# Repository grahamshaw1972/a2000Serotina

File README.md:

# A2000 Serotina Mechanical Keyboard

The A2000 Serotina Keyboard is a build it yourself Open Source Hardware Mechanical Keyboard for the Amiga A2000 and A3000 computers. Features are:

- Uses standard PC keyboard parts, case + keycaps

- Allows the use of the WASD keycap printing service for Amiga specific keycaps

- All soldering is Through Hole - no SMD soldering required

- No original A2000 keyboard parts required

- All electronic components are still available to buy

- Uses an Arduino micro-controller

- Uses Cherry MX type switches

- Uses QMK firmware ( with Amiga specific code added )

- Multiple QMK keymaps supported for regional key variations

- Plugs directly in to an A2000 or A3000 using the 5 pin Din connector - no USB required

Jan Beta has done an excellent build video for this keyboard. Please take a look:
https://youtu.be/dw3RDYq1Pn0?si=XJSP298tZxawzPFw

The keyboard layout for the UK keymap looks like this: 

The PCB for V1.5 looks like this: 

When the build is completed, V1.4 looks like this: 

A family portrait. The V1.4 Serotina keyboard with it's bigger brother and the inspiration for the project.

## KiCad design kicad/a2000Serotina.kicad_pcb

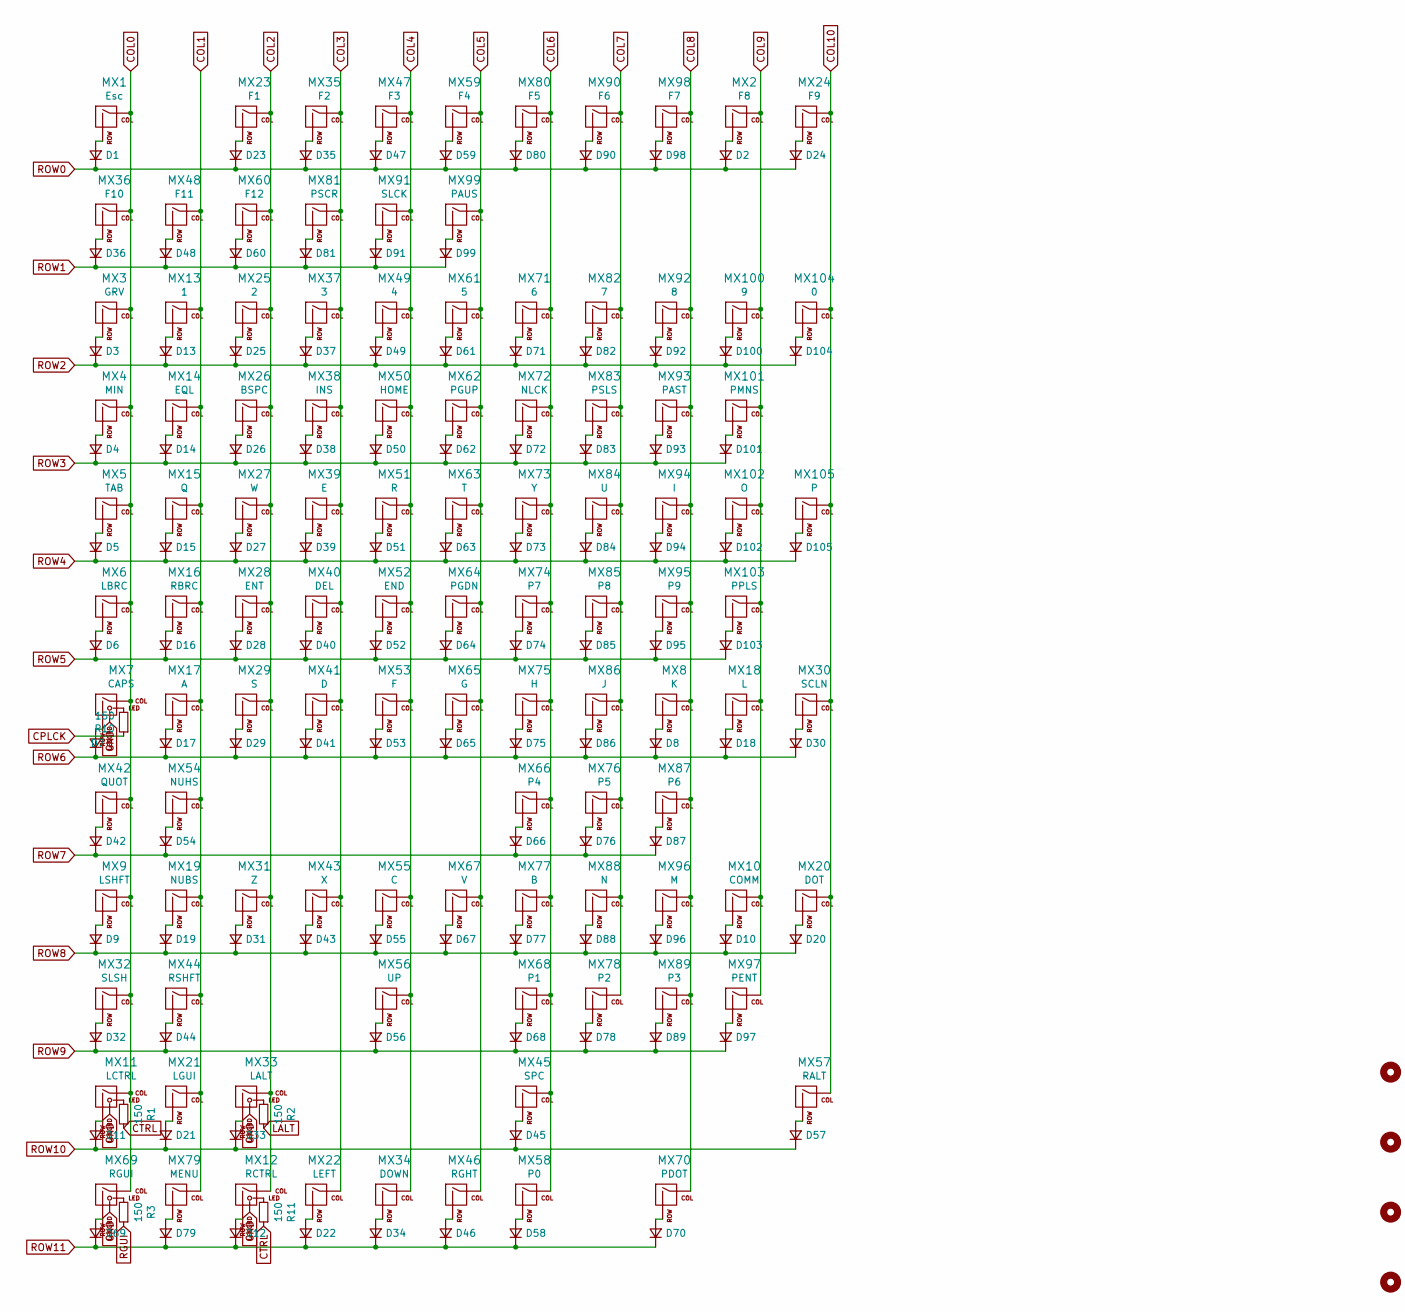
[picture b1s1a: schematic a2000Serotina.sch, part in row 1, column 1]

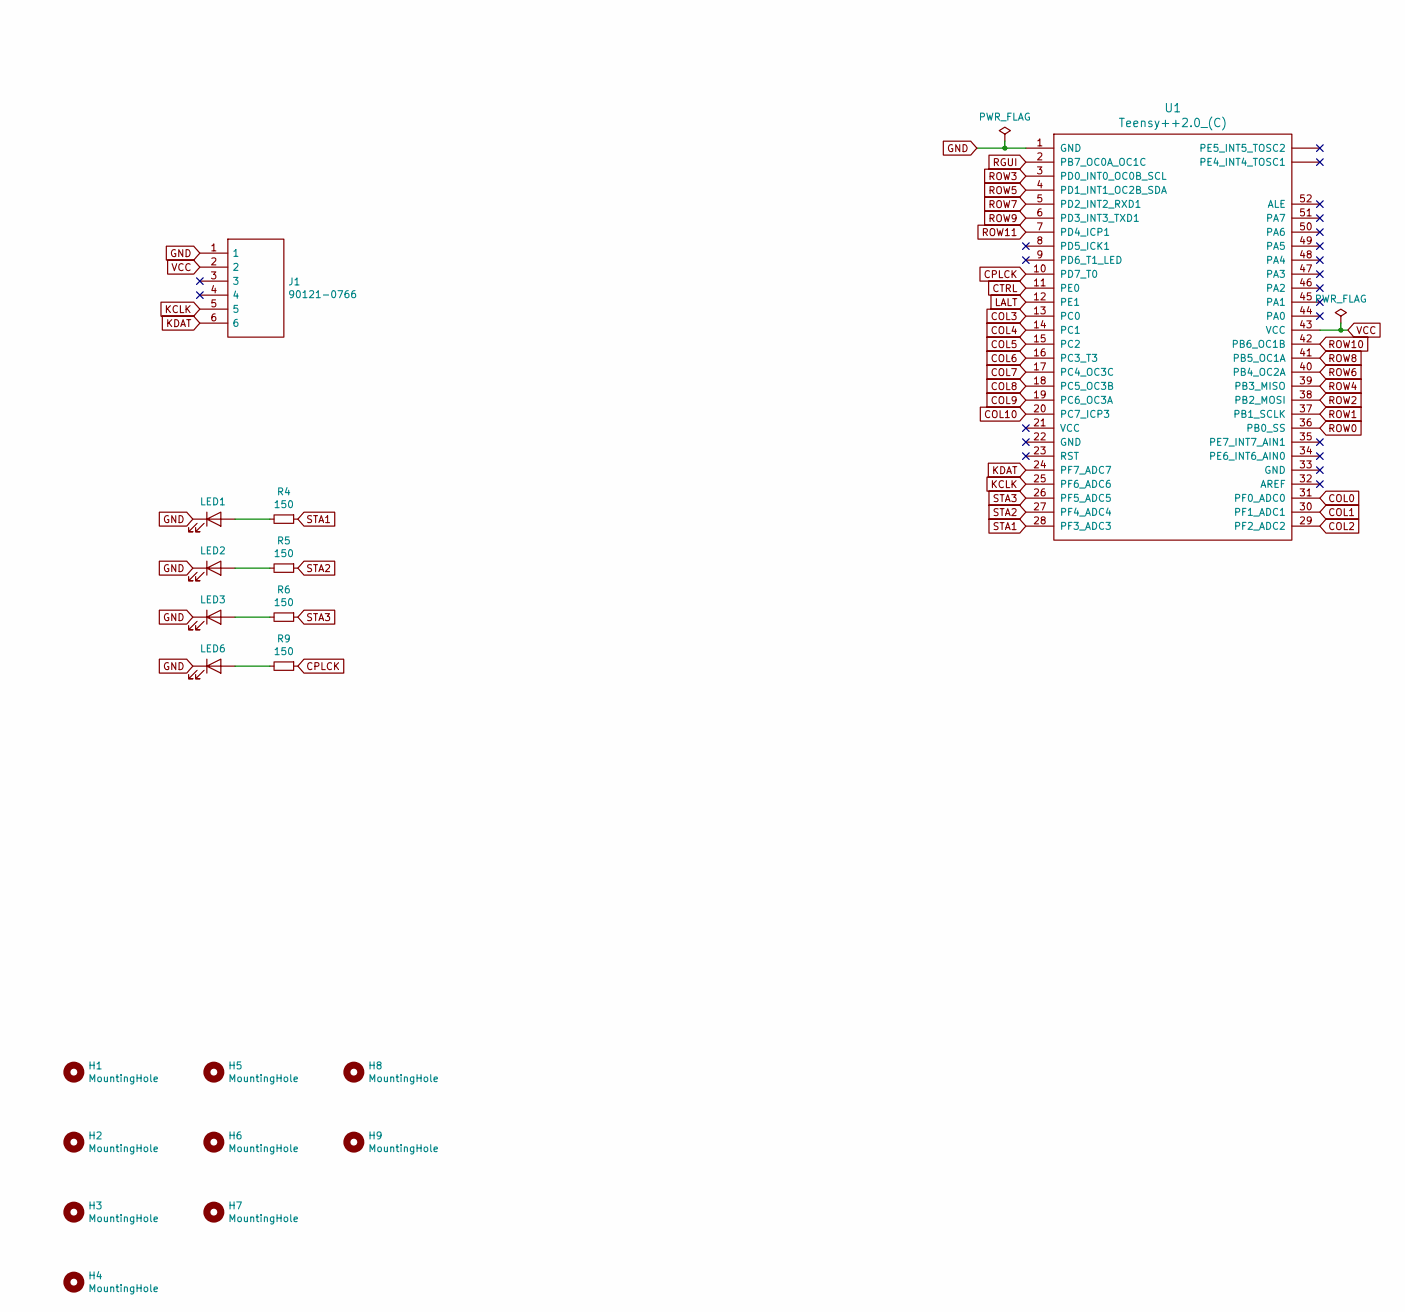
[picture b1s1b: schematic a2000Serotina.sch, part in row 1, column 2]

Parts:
D1, D2, D3, D4, D5, D6, D7, D8, D9, D10, D11, D12, D13, D14, D15, D16, D17, D18, D19, D20, D21, D22, D23, D24, D25, D26, D27, D28, D29, D30, D31, D32, D33, D34, D35, D36, D37, D38, D39, D40, D41, D42, D43, D44, D45, D46, D47, D48, D49, D50, D51, D52, D53, D54, D55, D56, D57, D58, D59, D60, D61, D62, D63, D64, D65, D66, D67, D68, D69, D70, D71, D72, D73, D74, D75, D76, D77, D78, D79, D80, D81, D82, D83, D84, D85, D86, D87, D88, D89, D90, D91, D92, D93, D94, D95, D96, D97, D98, D99, D100, D101, D102, D103, D104, D105: D_Small; D_DO-35_SOD27_P7.62mm_Horizontal
H1, H2, H3, H4: MountingHole; MountingHole_6.4mm_M6
H5, H6, H7: MountingHole; MountingHole_8.4mm_M8
H8, H9: MountingHole; MountingHole_2.5mm
J1: 90121-0766; 901210766; Mouser Part Number 538-90121-0766
LED1, LED2, LED3, LED6: LED; LED_D3.0mm
MX1, MX2, MX3, MX4, MX6, MX8, MX10, MX13, MX14, MX15, MX16, MX17, MX18, MX19, MX20, MX22, MX23, MX24, MX25, MX27, MX29, MX30, MX31, MX32, MX34, MX35, MX36, MX37, MX38, MX39, MX40, MX41, MX42, MX43, MX46, MX47, MX48, MX49, MX50, MX51, MX52, MX53, MX54, MX55, MX56, MX59, MX60, MX61, MX62, MX63, MX64, MX65, MX66, MX67, MX68, MX70, MX71, MX72, MX73, MX74, MX75, MX76, MX77, MX78, MX80, MX81, MX82, MX83, MX84, MX85, MX86, MX87, MX88, MX89, MX90, MX91, MX92, MX93, MX94, MX95, MX96, MX98, MX99, MX100, MX101, MX102, MX104, MX105: MX-NoLED; MX-1U-NoLED
MX5: MX-NoLED; MX-1.5U-NoLED
MX7: MX-LED; MX-1.75U
MX9, MX21, MX57, MX79: MX-NoLED; MX-1.25U-NoLED
MX11, MX12, MX33, MX69: MX-LED; MX-1.25U
MX26, MX28, MX58, MX97, MX103: MX-NoLED; MX-2U-NoLED
MX44: MX-NoLED; MX-2.75U-NoLED
MX45: MX-NoLED; MX-6.25U-NoLED
R1, R2, R3, R4, R5, R6, R9, R10, R11: 150; R_Axial_DIN0207_L6.3mm_D2.5mm_P10.16mm_Horizontal
U1: Teensy++2.0_(C); Teensy2.0++

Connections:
COL0: MX1.1 (COL), MX3.1 (COL), MX4.1 (COL), MX5.1 (COL), MX6.1 (COL), MX7.1 (COL), MX9.1 (COL), MX11.1 (COL), MX32.1 (COL), MX36.1 (COL), MX42.1 (COL), MX69.1 (COL), U1.31 (PF0_ADC0)
COL1: MX13.1 (COL), MX14.1 (COL), MX15.1 (COL), MX16.1 (COL), MX17.1 (COL), MX19.1 (COL), MX21.1 (COL), MX44.1 (COL), MX48.1 (COL), MX54.1 (COL), MX79.1 (COL), U1.30 (PF1_ADC1)
COL2: MX12.1 (COL), MX23.1 (COL), MX25.1 (COL), MX26.1 (COL), MX27.1 (COL), MX28.1 (COL), MX29.1 (COL), MX31.1 (COL), MX33.1 (COL), MX60.1 (COL), U1.29 (PF2_ADC2)
COL3: MX22.1 (COL), MX35.1 (COL), MX37.1 (COL), MX38.1 (COL), MX39.1 (COL), MX40.1 (COL), MX41.1 (COL), MX43.1 (COL), MX81.1 (COL), U1.13 (PC0)
COL4: MX34.1 (COL), MX47.1 (COL), MX49.1 (COL), MX50.1 (COL), MX51.1 (COL), MX52.1 (COL), MX53.1 (COL), MX55.1 (COL), MX56.1 (COL), MX91.1 (COL), U1.14 (PC1)
COL5: MX46.1 (COL), MX59.1 (COL), MX61.1 (COL), MX62.1 (COL), MX63.1 (COL), MX64.1 (COL), MX65.1 (COL), MX67.1 (COL), MX99.1 (COL), U1.15 (PC2)
COL6: MX45.1 (COL), MX58.1 (COL), MX66.1 (COL), MX68.1 (COL), MX71.1 (COL), MX72.1 (COL), MX73.1 (COL), MX74.1 (COL), MX75.1 (COL), MX77.1 (COL), MX80.1 (COL), U1.16 (PC3_T3)
COL7: MX76.1 (COL), MX78.1 (COL), MX82.1 (COL), MX83.1 (COL), MX84.1 (COL), MX85.1 (COL), MX86.1 (COL), MX88.1 (COL), MX90.1 (COL), U1.17 (PC4_OC3C)
COL8: MX8.1 (COL), MX70.1 (COL), MX87.1 (COL), MX89.1 (COL), MX92.1 (COL), MX93.1 (COL), MX94.1 (COL), MX95.1 (COL), MX96.1 (COL), MX98.1 (COL), U1.18 (PC5_OC3B)
COL9: MX2.1 (COL), MX10.1 (COL), MX18.1 (COL), MX97.1 (COL), MX100.1 (COL), MX101.1 (COL), MX102.1 (COL), MX103.1 (COL), U1.19 (PC6_OC3A)
COL10: MX20.1 (COL), MX24.1 (COL), MX30.1 (COL), MX57.1 (COL), MX104.1 (COL), MX105.1 (COL), U1.20 (PC7_ICP3)
CPLCK: R9.1, R10.1, U1.10 (PD7_T0)
CTRL: R1.1, R11.1, U1.11 (PE0)
GND: J1.1, LED1.1 (K), LED2.1 (K), LED3.1 (K), LED6.1 (K), MX7.4 (LEDGND), MX11.4 (LEDGND), MX12.4 (LEDGND), MX33.4 (LEDGND), MX69.4 (LEDGND), U1.1 (GND)
KCLK: J1.5, U1.25 (PF6_ADC6)
KDAT: J1.6, U1.24 (PF7_ADC7)
LALT: R2.1, U1.12 (PE1)
unnamed: D1.2 (A), MX1.2 (ROW)
unnamed: D2.2 (A), MX2.2 (ROW)
unnamed: D3.2 (A), MX3.2 (ROW)
unnamed: D4.2 (A), MX4.2 (ROW)
unnamed: D5.2 (A), MX5.2 (ROW)
unnamed: D6.2 (A), MX6.2 (ROW)
unnamed: D7.2 (A), MX7.2 (ROW)
unnamed: D8.2 (A), MX8.2 (ROW)
unnamed: D9.2 (A), MX9.2 (ROW)
unnamed: D10.2 (A), MX10.2 (ROW)
unnamed: D11.2 (A), MX11.2 (ROW)
unnamed: D12.2 (A), MX12.2 (ROW)
unnamed: D13.2 (A), MX13.2 (ROW)
unnamed: D14.2 (A), MX14.2 (ROW)
unnamed: D15.2 (A), MX15.2 (ROW)
unnamed: D16.2 (A), MX16.2 (ROW)
unnamed: D17.2 (A), MX17.2 (ROW)
unnamed: D18.2 (A), MX18.2 (ROW)
unnamed: D19.2 (A), MX19.2 (ROW)
unnamed: D20.2 (A), MX20.2 (ROW)
unnamed: D21.2 (A), MX21.2 (ROW)
unnamed: D22.2 (A), MX22.2 (ROW)
unnamed: D23.2 (A), MX23.2 (ROW)
unnamed: D24.2 (A), MX24.2 (ROW)
unnamed: D25.2 (A), MX25.2 (ROW)
unnamed: D26.2 (A), MX26.2 (ROW)
unnamed: D27.2 (A), MX27.2 (ROW)
unnamed: D28.2 (A), MX28.2 (ROW)
unnamed: D29.2 (A), MX29.2 (ROW)
unnamed: D30.2 (A), MX30.2 (ROW)
unnamed: D31.2 (A), MX31.2 (ROW)
unnamed: D32.2 (A), MX32.2 (ROW)
unnamed: D33.2 (A), MX33.2 (ROW)
unnamed: D34.2 (A), MX34.2 (ROW)
unnamed: D35.2 (A), MX35.2 (ROW)
unnamed: D36.2 (A), MX36.2 (ROW)
unnamed: D37.2 (A), MX37.2 (ROW)
unnamed: D38.2 (A), MX38.2 (ROW)
unnamed: D39.2 (A), MX39.2 (ROW)
unnamed: D40.2 (A), MX40.2 (ROW)
unnamed: D41.2 (A), MX41.2 (ROW)
unnamed: D42.2 (A), MX42.2 (ROW)
unnamed: D43.2 (A), MX43.2 (ROW)
unnamed: D44.2 (A), MX44.2 (ROW)
unnamed: D45.2 (A), MX45.2 (ROW)
unnamed: D46.2 (A), MX46.2 (ROW)
unnamed: D47.2 (A), MX47.2 (ROW)
unnamed: D48.2 (A), MX48.2 (ROW)
unnamed: D49.2 (A), MX49.2 (ROW)
unnamed: D50.2 (A), MX50.2 (ROW)
unnamed: D51.2 (A), MX51.2 (ROW)
unnamed: D52.2 (A), MX52.2 (ROW)
unnamed: D53.2 (A), MX53.2 (ROW)
unnamed: D54.2 (A), MX54.2 (ROW)
unnamed: D55.2 (A), MX55.2 (ROW)
unnamed: D56.2 (A), MX56.2 (ROW)
unnamed: D57.2 (A), MX57.2 (ROW)
unnamed: D58.2 (A), MX58.2 (ROW)
unnamed: D59.2 (A), MX59.2 (ROW)
unnamed: D60.2 (A), MX60.2 (ROW)
unnamed: D61.2 (A), MX61.2 (ROW)
unnamed: D62.2 (A), MX62.2 (ROW)
unnamed: D63.2 (A), MX63.2 (ROW)
unnamed: D64.2 (A), MX64.2 (ROW)
unnamed: D65.2 (A), MX65.2 (ROW)
unnamed: D66.2 (A), MX66.2 (ROW)
unnamed: D67.2 (A), MX67.2 (ROW)
unnamed: D68.2 (A), MX68.2 (ROW)
unnamed: D69.2 (A), MX69.2 (ROW)
unnamed: D70.2 (A), MX70.2 (ROW)
unnamed: D71.2 (A), MX71.2 (ROW)
unnamed: D72.2 (A), MX72.2 (ROW)
unnamed: D73.2 (A), MX73.2 (ROW)
unnamed: D74.2 (A), MX74.2 (ROW)
unnamed: D75.2 (A), MX75.2 (ROW)
unnamed: D76.2 (A), MX76.2 (ROW)
unnamed: D77.2 (A), MX77.2 (ROW)
unnamed: D78.2 (A), MX78.2 (ROW)
unnamed: D79.2 (A), MX79.2 (ROW)
unnamed: D80.2 (A), MX80.2 (ROW)
unnamed: D81.2 (A), MX81.2 (ROW)
unnamed: D82.2 (A), MX82.2 (ROW)
unnamed: D83.2 (A), MX83.2 (ROW)
unnamed: D84.2 (A), MX84.2 (ROW)
unnamed: D85.2 (A), MX85.2 (ROW)
unnamed: D86.2 (A), MX86.2 (ROW)
unnamed: D87.2 (A), MX87.2 (ROW)
unnamed: D88.2 (A), MX88.2 (ROW)
unnamed: D89.2 (A), MX89.2 (ROW)
unnamed: D90.2 (A), MX90.2 (ROW)
unnamed: D91.2 (A), MX91.2 (ROW)
unnamed: D92.2 (A), MX92.2 (ROW)
unnamed: D93.2 (A), MX93.2 (ROW)
unnamed: D94.2 (A), MX94.2 (ROW)
unnamed: D95.2 (A), MX95.2 (ROW)
unnamed: D96.2 (A), MX96.2 (ROW)
unnamed: D97.2 (A), MX97.2 (ROW)
unnamed: D98.2 (A), MX98.2 (ROW)
unnamed: D99.2 (A), MX99.2 (ROW)
unnamed: D100.2 (A), MX100.2 (ROW)
unnamed: D101.2 (A), MX101.2 (ROW)
unnamed: D102.2 (A), MX102.2 (ROW)
unnamed: D103.2 (A), MX103.2 (ROW)
unnamed: D104.2 (A), MX104.2 (ROW)
unnamed: D105.2 (A), MX105.2 (ROW)
unnamed: LED1.2 (A), R4.2
unnamed: LED2.2 (A), R5.2
unnamed: LED3.2 (A), R6.2
unnamed: LED6.2 (A), R9.2
unnamed: MX7.3 (LED), R10.2
unnamed: MX11.3 (LED), R1.2
unnamed: MX12.3 (LED), R11.2
unnamed: MX33.3 (LED), R2.2
unnamed: MX69.3 (LED), R3.2
RGUI: R3.1, U1.2 (PB7_OC0A_OC1C)
ROW0: D1.1 (K), D2.1 (K), D23.1 (K), D24.1 (K), D35.1 (K), D47.1 (K), D59.1 (K), D80.1 (K), D90.1 (K), D98.1 (K), U1.36 (PB0_SS)
ROW1: D36.1 (K), D48.1 (K), D60.1 (K), D81.1 (K), D91.1 (K), D99.1 (K), U1.37 (PB1_SCLK)
ROW2: D3.1 (K), D13.1 (K), D25.1 (K), D37.1 (K), D49.1 (K), D61.1 (K), D71.1 (K), D82.1 (K), D92.1 (K), D100.1 (K), D104.1 (K), U1.38 (PB2_MOSI)
ROW3: D4.1 (K), D14.1 (K), D26.1 (K), D38.1 (K), D50.1 (K), D62.1 (K), D72.1 (K), D83.1 (K), D93.1 (K), D101.1 (K), U1.3 (PD0_INT0_OC0B_SCL)
ROW4: D5.1 (K), D15.1 (K), D27.1 (K), D39.1 (K), D51.1 (K), D63.1 (K), D73.1 (K), D84.1 (K), D94.1 (K), D102.1 (K), D105.1 (K), U1.39 (PB3_MISO)
ROW5: D6.1 (K), D16.1 (K), D28.1 (K), D40.1 (K), D52.1 (K), D64.1 (K), D74.1 (K), D85.1 (K), D95.1 (K), D103.1 (K), U1.4 (PD1_INT1_OC2B_SDA)
ROW6: D7.1 (K), D8.1 (K), D17.1 (K), D18.1 (K), D29.1 (K), D30.1 (K), D41.1 (K), D53.1 (K), D65.1 (K), D75.1 (K), D86.1 (K), U1.40 (PB4_OC2A)
ROW7: D42.1 (K), D54.1 (K), D66.1 (K), D76.1 (K), D87.1 (K), U1.5 (PD2_INT2_RXD1)
ROW8: D9.1 (K), D10.1 (K), D19.1 (K), D20.1 (K), D31.1 (K), D43.1 (K), D55.1 (K), D67.1 (K), D77.1 (K), D88.1 (K), D96.1 (K), U1.41 (PB5_OC1A)
ROW9: D32.1 (K), D44.1 (K), D56.1 (K), D68.1 (K), D78.1 (K), D89.1 (K), D97.1 (K), U1.6 (PD3_INT3_TXD1)
ROW10: D11.1 (K), D21.1 (K), D33.1 (K), D45.1 (K), D57.1 (K), U1.42 (PB6_OC1B)
ROW11: D12.1 (K), D22.1 (K), D34.1 (K), D46.1 (K), D58.1 (K), D69.1 (K), D70.1 (K), D79.1 (K), U1.7 (PD4_ICP1)
STA1: R4.1, U1.28 (PF3_ADC3)
STA2: R5.1, U1.27 (PF4_ADC4)
STA3: R6.1, U1.26 (PF5_ADC5)
VCC: J1.2, U1.43 (VCC)

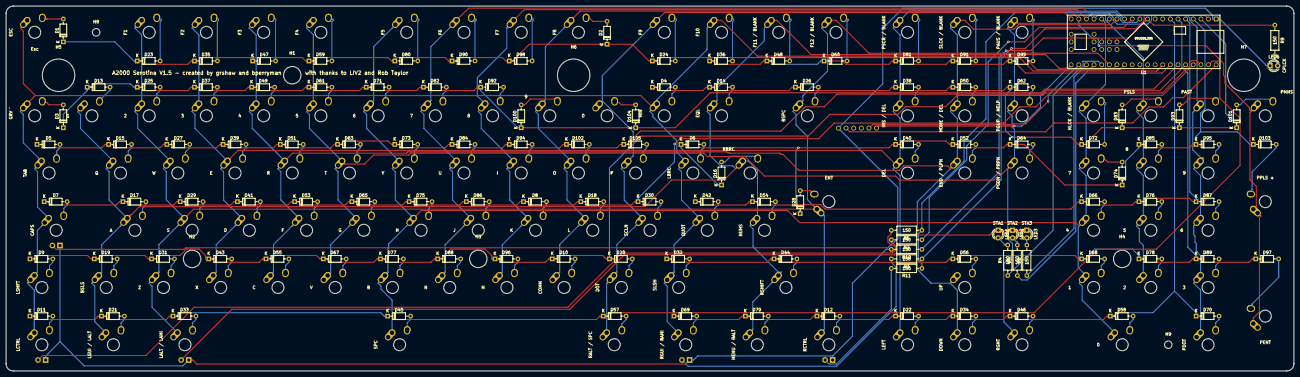
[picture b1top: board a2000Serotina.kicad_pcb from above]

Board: 2 copper layers, 428.6 x 121.4 mm, 234 parts (1 on the bottom side), 148 nets.

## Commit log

2021-06-23 Worked out Keyboard Layou
    Added Keyboard Layout Editor Layout
    Added InkScape files.
2021-07-04 Create Kicad project
2021-07-04 Add submodules
2021-07-04 Add Kicad Symbol & Footprint libraries.
2021-07-04 Add submodules teensy_library and teensy.pretty
2021-07-04 Add teensy kicad lib
2021-07-04 Add Footprints and layouts for Samacsys Library Loader
    This allows ECAD models to be downloaded directly from Mouser.
2021-07-04 Wiring planned out.
    Used Keyboard Firmware Builder to design Wiring layout.
    Added various design files for wiring layout.
    Also added a2000serotina.zip which contain QMK firmware ( needs to be updated )
2021-07-04 Some work on the Schema
2021-07-05 Further work on Keyboard Matrix
2021-07-06 Matrix now complete.
2021-07-07 Connections and wiring complete
    Now working on PCB Footprints.
2021-07-08 All footprints now assigned
2021-07-08 Work on PCB Layout
2021-07-08 All switches now placed.
2021-07-08 All Components now placed on PCB
2021-07-09 Auto routing complete
2021-07-09 Add picture of the PCB to README.md
2021-07-09 Update pcbV1_0.PNG
    Increased resolution of PCB image
2021-07-09 Fix PCB layout
    Move Diodes that are too close to Stabilizer drill holes.
2021-07-10 Generated Gerber Files and Bill of Materials
2021-07-10 Added Text Labels to Front Silkscreen
    Added letter labels for Mx Switches
    Added labels for LEDs
    Sorted out Resistor footprints so that vaules are visible on Front Silkscreen.
2021-07-10 Add renderV1_0.png
    And include in README.md
2021-07-11 Update to PCB
    Moved DIN socket and CPU nearer to edge of PCB.
2021-07-11 Added qmk_firmware
2021-07-11 Use TeensyNumPad config in firmware
2021-07-11 Change Row 6 Pin from D6 to F2
    D6 lights the LED on the Teensy 2.0 ++ - better to have D6 control a LED.
2021-07-14 Updated column / row layout of switches
    Now much more regular on the bottom rows.
2021-07-14 Update pictures
2021-07-21 Updated readme with picture of the real PCB
2021-07-25 V1.0 Build and Bug fixes following fault finding
2021-07-28 Add Definitions for LED pins
    In config.h:
    #define LED_NUM_LOCK_PIN D5
    #define LED_CAPS_LOCK_PIN D7
    #define LED_SCROLL_LOCK_PIN D6
    Also light LEDS STA1 + STA2 if 2 or 3 keys are pressed simulaneously.
2021-07-29 Add signature lighting of Amiga key LEDS
    Light LEDS in keys when each of the Amiga Reset keys is pressed.
    LCTRL, LAMI, RAMI on the Amiga keyboard.
    Which maps to LCTRL, LALT, RGUI on the PC keyboard.
2021-07-31 Add Amiga Keycodes
2021-07-31 Completed amiga_keycode_table
2021-08-01 Reset Amiga now working.
2021-08-01 Change AKC_NUBS to AKC_LSFT
    Also update Inkscape files with same change.
2021-08-01 Add Mounting holes
2021-08-03 Change 5 Pin Din to right angle pin headers
    So that a case will fit on.
2021-08-04 Move and rotate right angle pin header
2021-08-08 Fixes to firmware
    1) Fix bug where Pressing Enter and small Enter together causes lock up. In fact pressing any two keys mapped to the same Amiga keys was causing a problem. Now fixed
    2) Disable Caps Lock on Amiga. This was causing odd behaviour. Notes on the behaviour are:
    Caps Lock -> an alpha character, results in q bogus character being repeated e.g
    a 0x20 -> q 0x10
    s 0x21 -> nothing
    d 0x22 -> w 0x11
2021-08-08 Add Support for US Layout.
    Add Support for US Layout.
    Also fix bug where P0 was being ignored on Amiga:
    if(keycode != AKC_CAPS) -> if(amigaKeyCode != AKC_CAPS)
    AKC_CAPS is 0x62, QMK key for code 0x62 is P0. So code was previously ignoring P0, not Caps Lock at all.
2021-08-08 Enable Caps Lock to work somewhat
    Now behaves like shift.
2021-08-14 Caps Lock now working.
    In order to get Caps Lock working, the Caps Lock control logic was integrated into the key counting logic. Additionally, the logicalKeyPressed concept was introduced.
2021-08-14 Change .gitignore for .hex files
    Now includes a2000Serotina_us_uk.hex
2021-08-14 Fix link in README.md
2021-08-16 Add Build Instructions
    Add Build Instructions
2021-08-16 Rename buildInstructions.md
    to README.md
2021-08-17 Update firmware to flash all LEDs on start up
    Flash all LEDs for 1s on start up.
2021-08-18 Updated PCB design, fitting into case
    1) Add extra CTRL_LED in Right Ctrl Key DONE
    2) Add extra CAPS_LED in top right LED6 R9 ( Previously KCLK ) DONE
    CAPS_LOCK NUM_LOCK SCR_LOCK
    3) Move NMLCK + SCLCK LEDs to top right DONE
    4) Fix font on second half of Thank you message DONE
    with thanks to LIV2 and Rob Taylor
2021-08-19 Update README.md, changing Build Complete Picture
    Change from V1.0 to V1.2 - now in case.
2021-08-20 Update Build Instructions
    Build instructions are now complete - using V1.1 PCB
2021-08-20 Fix problem with UK Layout in Inkscape
    Key to Right of Left Shift was showing as a second Shift key. Change to \
2021-08-20 Added support for German Keymap
    Added Inkscape files.
    Added international keymap.
2021-08-21 Fix Bug with duplicate keycodes when keys being released
    Also Simplify Caps Lock Pressed logic. Now uses mod 2.
2021-08-30 V1.3 Design Complete
2021-09-05 Change for V1.4
    Now uses a mounting plate from WASD.
    1) Adjust dimensions to match WASD PCB
    2) Make mounting holes bigger so that PCB sits lower
    3) Move resistors so that they are not under plate
    4) Move Caps Lock LED to rightmost and move Teensy back to top.
    5) J1 moved between Enter + Del
2021-09-06 V1.5
    1) Remove PCB mount holes from switch footprints. DONE
2021-09-13 Update Build instructions
    Now covers a build using the v1.4 PCB.
2021-09-19 Add a2000Serotina_pc_testing_uk.hex
    Also complete V1.4 Build instructions and update main README.md with V1.4 pictures.
2021-09-25 Add Flash Firmware Instructions
    Also Update Build instructions.
2021-09-25 Update Build and Flashing Firmware Instructions
    Adding Cross Links in each case.
2021-09-25 Update flashingFirmware/README.md
    URLS updated.
2021-09-25 Update BOM sheet + Build Instructions
2021-09-25 Update Ordering from WASD instructions
2021-09-25 Add PCB Printing instructions.
2021-10-03 Add two additional mounting holes
    To match WASD PCB.
2021-10-24 Updated first half of Build instructions to v1.5
    V1.5 PCB complete.
2021-10-31 Completed V1.5 Build and instructions
2021-10-31 Tidy up Build Instructions
2021-11-02 Create LICENSE
2021-11-06 Remove Build Steps column from BOM sheet
2021-11-06 Update Build Instructions
